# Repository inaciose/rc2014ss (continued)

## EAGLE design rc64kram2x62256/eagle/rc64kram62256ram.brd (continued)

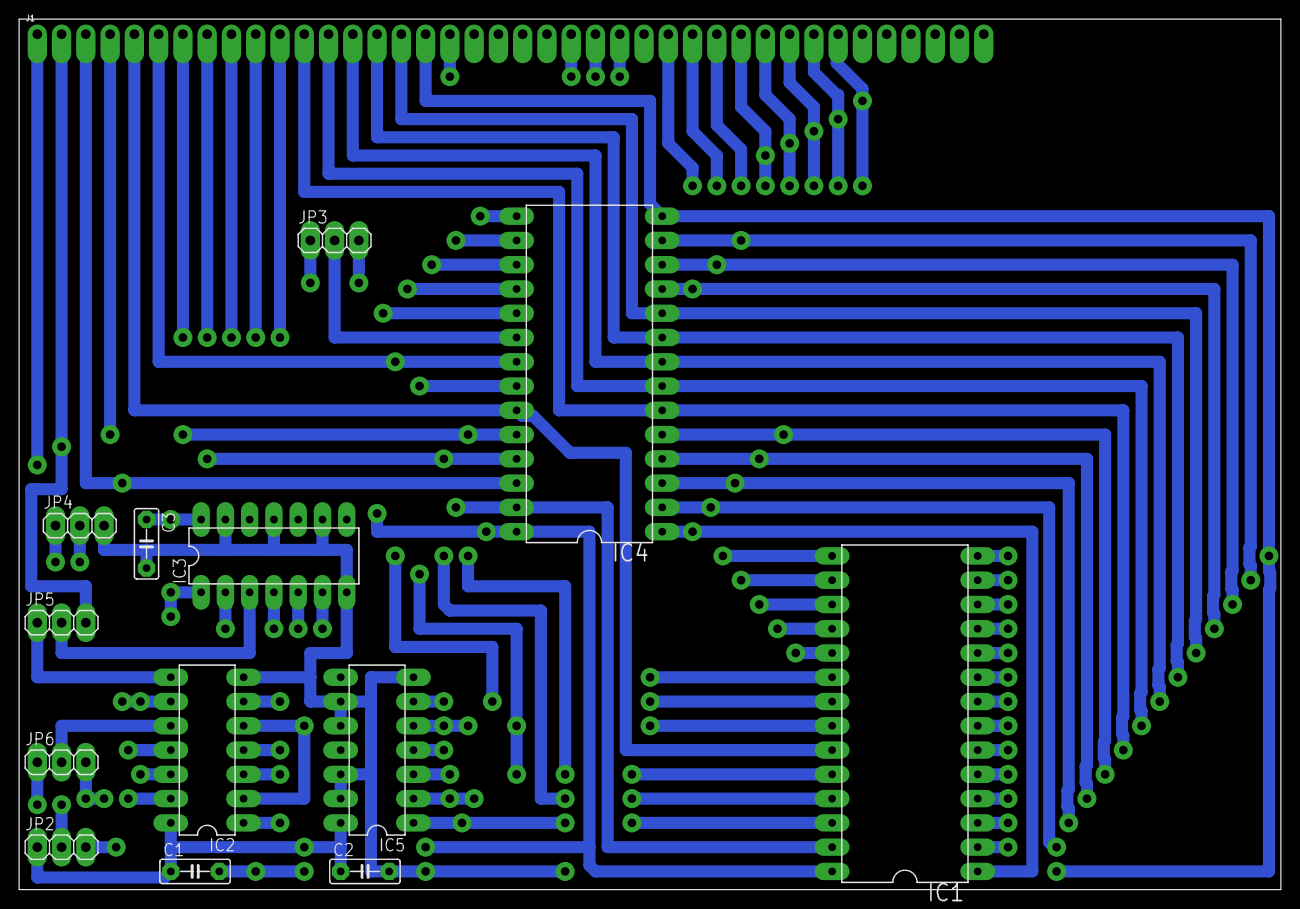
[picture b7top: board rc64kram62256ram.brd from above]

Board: 2 copper layers, 132.1 x 91.1 mm, 14 parts (0 on the bottom side), 43 nets.

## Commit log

2022-01-24 Create pcb
2022-01-24 Z80 board v1
2022-01-24 pdf for z80 board
2022-01-24 Delete eagle.epf
    file not needed deleted
2022-02-02 clock_v1 & cpu_v2
2022-02-28 new boards and some fixes
2024-01-28 Create unit2
2024-03-18 initial upload
2024-03-18 vga terminal hardware made perfboard
2024-03-21 Rename IMG20240204143856.jpg to img-test-with-breadbord-1.jpg
2024-03-21 restore file
2024-04-01 Create ztgSDcardGALs
2024-04-01 ztgSDcardB.txt change some pins, and set all unused output pins
2024-04-01 ztgSDcardA.txt set unused output pins
2024-04-01 Update ztgSDcardGALs
2024-04-05 global revision with additions
2024-05-25 Rename 68kbuses.txt to 68k/68kbuses.txt
2024-05-25 Rename 68kresets.txt to 68k/68kresets.txt
2024-05-25 Rename 68k/68kresets.txt to 68k/reset/readme.txt
